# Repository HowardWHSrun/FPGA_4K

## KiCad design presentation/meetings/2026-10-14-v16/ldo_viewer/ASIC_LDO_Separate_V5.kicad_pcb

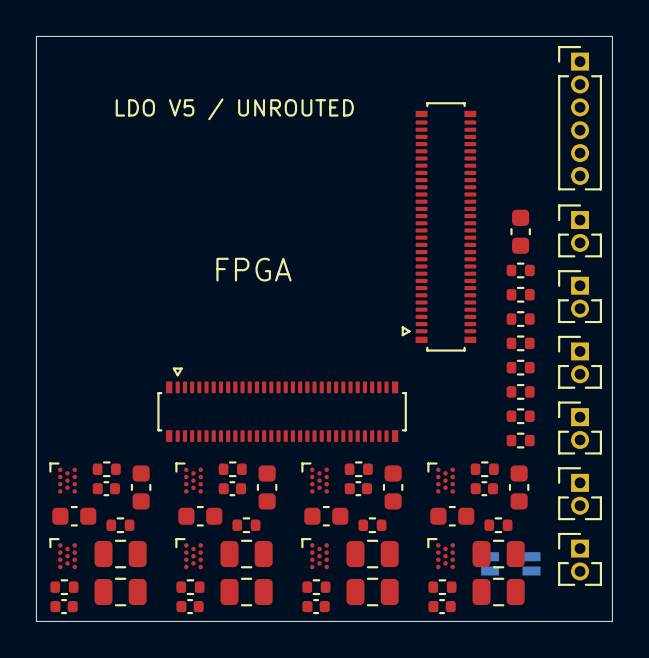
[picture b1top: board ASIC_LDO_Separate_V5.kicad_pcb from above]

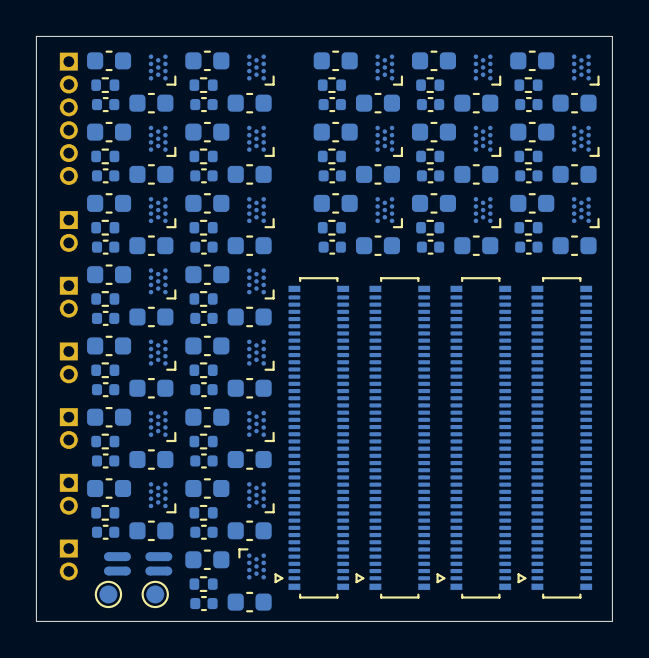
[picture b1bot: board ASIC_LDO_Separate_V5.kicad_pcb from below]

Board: 2 copper layers, 32.0 x 32.5 mm, 192 parts (130 on the bottom side), 203 nets, no tracks yet.

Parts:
C90: 10uF 10V - provisional bulk; C_0603_1608Metric
C101, C103, C104, C106, C107, C109, C110, C112, C113, C115, C116, C118, C119, C121, C201, C203, C204, C206, C207, C209, C210, C212, C213, C215, C216, C218, C219, C221, C301, C303, C304, C306, C307, C309, C310, C312, C313, C315, C316, C318, C319, C321, C401, C403, C404, C406, C407, C409, C410, C412, C413, C415, C416, C418, C419, C421: 10uF 10V; C_0603_1608Metric
C102, C105, C108, C111, C114, C117, C120, C202, C205, C208, C211, C214, C217, C220, C302, C305, C308, C311, C314, C317, C320, C402, C405, C408, C411, C414, C417, C420: 1uF 10V; C_0402_1005Metric
C122, C124, C222, C224, C322, C324, C422, C424: 10uF 25V; C_0805_2012Metric
C123, C223, C323, C423: 1uF 25V; C_0402_1005Metric
J1, J2: DF40C-60DP-0.4V(51); Hirose_DF40C-60DP-0.4V_2x30-1MP_P0.4mm
J10: ASIC 3.3 V external input; Harwin_M50-3530242_1x02_P1.27mm_Vertical
J90: Positive high-rail raw input; Harwin_M50-3530242_1x02_P1.27mm_Vertical
J91: Four regulated VSS10 inputs + returns; Harwin_M50-3530642_1x06_P1.27mm_Vertical
J101, J201, J301, J401: DF40C-80DP-0.4V(51); Hirose_DF40C-80DP-0.4V_2x40-1MP_P0.4mm
J102, J202, J302, J402: AC_IN provision - external analog source; Harwin_M50-3530242_1x02_P1.27mm_Vertical
NT100, NT200, NT300, NT400: AGND / DGND bond; NetTie-2_SMD_Pad0.5mm
R101, R102, R103, R104, R105, R201, R202, R203, R204, R205, R301, R302, R303, R304, R305, R401, R402, R403, R404, R405: 15k 1%; R_0402_1005Metric
R106, R206, R306, R406: 16k 1%; R_0402_1005Metric
R107, R207, R307, R407: 7.5k 1%; R_0402_1005Metric
R108, R208, R308, R408: 90k 1%; R_0402_1005Metric
R109, R209, R309, R409: 68k 1%; R_0402_1005Metric
R250, R251, R252, R253, R450, R451, R452, R453: 10k 1%; R_0402_1005Metric
TP90: ASIC_3V3 probe; TestPoint_Pad_D1.0mm
TP91: GND probe; TestPoint_Pad_D1.0mm
U101, U102, U103, U104, U105, U106, U107, U108, U201, U202, U203, U204, U205, U206, U207, U208, U301, U302, U303, U304, U305, U306, U307, U308, U401, U402, U403, U404, U405, U406, U407, U408: LT3046ANQ+T; LT3046_WLCSP_11_NQ

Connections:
ASIC1_CLK32MHz_Out: J1.9, J101.45
ASIC1_DATA1: J1.1, J101.79
ASIC1_DATA2: J1.2, J101.77
ASIC1_DATA3: J1.3, J101.75
ASIC1_DATA4: J1.4, J101.73
ASIC1_DATA5: J1.5, J101.43
ASIC1_DATA6: J1.6, J101.41
ASIC1_DATA7: J1.7, J101.39
ASIC1_DATA8: J1.8, J101.37
ASIC1_READ: J1.10, J101.35
ASIC1_SYNC: J1.11, J101.47
ASIC2_CLK32MHz_Out: J1.20, J101.19
ASIC2_DATA1: J1.12, J101.33
ASIC2_DATA2: J1.13, J101.31
ASIC2_DATA3: J1.14, J101.29
ASIC2_DATA4: J1.15, J101.27
ASIC2_DATA5: J1.16, J101.17
ASIC2_DATA6: J1.17, J101.15
ASIC2_DATA7: J1.18, J101.13
ASIC2_DATA8: J1.19, J101.11
ASIC2_READ: J1.21, J101.9
ASIC2_SYNC: J1.22, J101.21
ASIC3_CLK32MHz_Out: J1.32, J201.45
ASIC3_DATA1: J1.23, J201.79
ASIC3_DATA2: J1.24, J201.77
ASIC3_DATA3: J1.25, J201.75
ASIC3_DATA4: J1.26, J201.73
ASIC3_DATA5: J1.27, J201.43
ASIC3_DATA6: J1.28, J201.41
ASIC3_DATA7: J1.29, J201.39
ASIC3_DATA8: J1.31, J201.37
ASIC3_READ: J1.33, J201.35
ASIC3_SYNC: J1.34, J201.47
ASIC4_CLK32MHz_Out: J1.43, J201.19
ASIC4_DATA1: J1.35, J201.33
ASIC4_DATA2: J1.36, J201.31
ASIC4_DATA3: J1.37, J201.29
ASIC4_DATA4: J1.38, J201.27
ASIC4_DATA5: J1.39, J201.17
ASIC4_DATA6: J1.40, J201.15
ASIC4_DATA7: J1.41, J201.13
ASIC4_DATA8: J1.42, J201.11
ASIC4_READ: J1.44, J201.9
ASIC4_SYNC: J1.45, J201.21
ASIC5_CLK32MHz_Out: J2.9, J301.45
ASIC5_DATA1: J2.1, J301.79
ASIC5_DATA2: J2.2, J301.77
ASIC5_DATA3: J2.3, J301.75
ASIC5_DATA4: J2.4, J301.73
ASIC5_DATA5: J2.5, J301.43
ASIC5_DATA6: J2.6, J301.41
ASIC5_DATA7: J2.7, J301.39
ASIC5_DATA8: J2.8, J301.37
ASIC5_READ: J2.10, J301.35
ASIC5_SYNC: J2.11, J301.47
ASIC6_CLK32MHz_Out: J2.20, J301.19
ASIC6_DATA1: J2.12, J301.33
ASIC6_DATA2: J2.13, J301.31
ASIC6_DATA3: J2.14, J301.29
ASIC6_DATA4: J2.15, J301.27
ASIC6_DATA5: J2.16, J301.17
ASIC6_DATA6: J2.17, J301.15
ASIC6_DATA7: J2.18, J301.13
ASIC6_DATA8: J2.19, J301.11
ASIC6_READ: J2.21, J301.9
ASIC6_SYNC: J2.22, J301.21
ASIC7_CLK32MHz_Out: J2.32, J401.45
ASIC7_DATA1: J2.23, J401.79
ASIC7_DATA2: J2.24, J401.77
ASIC7_DATA3: J2.25, J401.75
ASIC7_DATA4: J2.26, J401.73
ASIC7_DATA5: J2.27, J401.43
ASIC7_DATA6: J2.28, J401.41
ASIC7_DATA7: J2.29, J401.39
ASIC7_DATA8: J2.31, J401.37
ASIC7_READ: J2.33, J401.35
ASIC7_SYNC: J2.34, J401.47
ASIC8_CLK32MHz_Out: J2.43, J401.19
ASIC8_DATA1: J2.35, J401.33
ASIC8_DATA2: J2.36, J401.31
ASIC8_DATA3: J2.37, J401.29
ASIC8_DATA4: J2.38, J401.27
ASIC8_DATA5: J2.39, J401.17
ASIC8_DATA6: J2.40, J401.15
ASIC8_DATA7: J2.41, J401.13
ASIC8_DATA8: J2.42, J401.11
ASIC8_READ: J2.44, J401.9
ASIC8_SYNC: J2.45, J401.21
ASIC_3V3: C90.1, C101.1, C104.1, C107.1, C110.1, C113.1, C116.1, C119.1, C201.1, C204.1, C207.1, C210.1, C213.1, C216.1, C219.1, C301.1, C304.1, C307.1, C310.1, C313.1, C316.1, C319.1, C401.1, C404.1, C407.1, C410.1, C413.1, C416.1, C419.1, J10.1, TP90.1 (1_1), U101.A3 (IN), U101.B3 (EN/UV), U101.F1 (PGFB), U102.A3 (IN), U102.B3 (EN/UV), U102.F1 (PGFB), U103.A3 (IN), U103.B3 (EN/UV), U103.F1 (PGFB), U104.A3 (IN), U104.B3 (EN/UV), U104.F1 (PGFB), U105.A3 (IN), U105.B3 (EN/UV), U105.F1 (PGFB), U106.A3 (IN), U106.B3 (EN/UV), U106.F1 (PGFB), U107.A3 (IN), U107.B3 (EN/UV), U107.F1 (PGFB), U201.A3 (IN), U201.B3 (EN/UV), U201.F1 (PGFB), U202.A3 (IN), U202.B3 (EN/UV), U202.F1 (PGFB), U203.A3 (IN), U203.B3 (EN/UV), U203.F1 (PGFB), U204.A3 (IN), U204.B3 (EN/UV), U204.F1 (PGFB), U205.A3 (IN), U205.B3 (EN/UV), U205.F1 (PGFB), U206.A3 (IN), U206.B3 (EN/UV), U206.F1 (PGFB), U207.A3 (IN), U207.B3 (EN/UV), U207.F1 (PGFB), U301.A3 (IN), U301.B3 (EN/UV), U301.F1 (PGFB), U302.A3 (IN), U302.B3 (EN/UV), U302.F1 (PGFB), U303.A3 (IN), U303.B3 (EN/UV), U303.F1 (PGFB), U304.A3 (IN), U304.B3 (EN/UV), U304.F1 (PGFB), U305.A3 (IN), U305.B3 (EN/UV), U305.F1 (PGFB), U306.A3 (IN), U306.B3 (EN/UV), U306.F1 (PGFB), U307.A3 (IN), U307.B3 (EN/UV), U307.F1 (PGFB), U401.A3 (IN), U401.B3 (EN/UV), U401.F1 (PGFB), U402.A3 (IN), U402.B3 (EN/UV), U402.F1 (PGFB), U403.A3 (IN), U403.B3 (EN/UV), U403.F1 (PGFB), U404.A3 (IN), U404.B3 (EN/UV), U404.F1 (PGFB), U405.A3 (IN), U405.B3 (EN/UV), U405.F1 (PGFB), U406.A3 (IN), U406.B3 (EN/UV), U406.F1 (PGFB), U407.A3 (IN), U407.B3 (EN/UV), U407.F1 (PGFB)
B1_AC_IN: J101.69, J102.1
B1_AGND: C101.2, C102.2, C103.2, C107.2, C108.2, C109.2, C110.2, C111.2, C112.2, C113.2, C114.2, C115.2, C116.2, C117.2, C118.2, C119.2, C120.2, C121.2, C122.2, C123.2, C124.2, J101.42, J101.44, J102.2, NT100.1, R101.2, R103.2, R104.2, R105.2, R106.2, R107.2, R108.2, R109.2, U101.E1 (GND), U101.F3 (ILIM), U103.E1 (GND), U103.F3 (ILIM), U104.E1 (GND), U104.F3 (ILIM), U105.E1 (GND), U105.F3 (ILIM), U106.E1 (GND), U106.F3 (ILIM), U107.E1 (GND), U107.F3 (ILIM), U108.E1 (GND), U108.F3 (ILIM)
B1_DVDD: C112.1, J101.34, U104.A1 (OUT), U104.Aa2 (OUT), U104.B1 (OUTS)
B1_REF_VCM: C121.1, J101.40, R109.1, U107.A1 (OUT), U107.Aa2 (OUT), U107.B1 (OUTS)
B1_REF_VDD: C115.1, J101.52, U105.A1 (OUT), U105.Aa2 (OUT), U105.B1 (OUTS)
B1_VDD10: C124.1, J101.36, U108.A1 (OUT), U108.Aa2 (OUT), U108.B1 (OUTS)
B1_VDD_ADC: C106.1, J101.56, U102.A1 (OUT), U102.Aa2 (OUT), U102.B1 (OUTS)
B1_VDD_CGEN: C118.1, J101.1, U106.A1 (OUT), U106.Aa2 (OUT), U106.B1 (OUTS)
B1_VDD_DRIVER: C109.1, J101.38, U103.A1 (OUT), U103.Aa2 (OUT), U103.B1 (OUTS)
B1_VDD_FE: C103.1, J101.50, U101.A1 (OUT), U101.Aa2 (OUT), U101.B1 (OUTS)
B1_VSS10: J91.2, J101.54
B2_AC_IN: J201.69, J202.1
B2_AGND: C201.2, C202.2, C203.2, C207.2, C208.2, C209.2, C210.2, C211.2, C212.2, C213.2, C214.2, C215.2, C216.2, C217.2, C218.2, C219.2, C220.2, C221.2, C222.2, C223.2, C224.2, J201.42, J201.44, J202.2, NT200.1, R201.2, R203.2, R204.2, R205.2, R206.2, R207.2, R208.2, R209.2, U201.E1 (GND), U201.F3 (ILIM), U203.E1 (GND), U203.F3 (ILIM), U204.E1 (GND), U204.F3 (ILIM), U205.E1 (GND), U205.F3 (ILIM), U206.E1 (GND), U206.F3 (ILIM), U207.E1 (GND), U207.F3 (ILIM), U208.E1 (GND), U208.F3 (ILIM)
B2_DVDD: C212.1, J201.34, U204.A1 (OUT), U204.Aa2 (OUT), U204.B1 (OUTS)
B2_REF_VCM: C221.1, J201.40, R209.1, U207.A1 (OUT), U207.Aa2 (OUT), U207.B1 (OUTS)
B2_REF_VDD: C215.1, J201.52, U205.A1 (OUT), U205.Aa2 (OUT), U205.B1 (OUTS)
B2_STIM_CHB_IDLE: J201.49, R250.1
B2_STIM_CLK_IDLE: J201.53, R252.1
B2_STIM_EN_IDLE: J201.51, R251.1
B2_STIM_START_IDLE: J201.55, R253.1
B2_VDD10: C224.1, J201.36, U208.A1 (OUT), U208.Aa2 (OUT), U208.B1 (OUTS)
B2_VDD_ADC: C206.1, J201.56, U202.A1 (OUT), U202.Aa2 (OUT), U202.B1 (OUTS)
B2_VDD_CGEN: C218.1, J201.1, U206.A1 (OUT), U206.Aa2 (OUT), U206.B1 (OUTS)
B2_VDD_DRIVER: C209.1, J201.38, U203.A1 (OUT), U203.Aa2 (OUT), U203.B1 (OUTS)
B2_VDD_FE: C203.1, J201.50, U201.A1 (OUT), U201.Aa2 (OUT), U201.B1 (OUTS)
B2_VSS10: J91.3, J201.54
B3_AC_IN: J301.69, J302.1
B3_AGND: C301.2, C302.2, C303.2, C307.2, C308.2, C309.2, C310.2, C311.2, C312.2, C313.2, C314.2, C315.2, C316.2, C317.2, C318.2, C319.2, C320.2, C321.2, C322.2, C323.2, C324.2, J301.42, J301.44, J302.2, NT300.1, R301.2, R303.2, R304.2, R305.2, R306.2, R307.2, R308.2, R309.2, U301.E1 (GND), U301.F3 (ILIM), U303.E1 (GND), U303.F3 (ILIM), U304.E1 (GND), U304.F3 (ILIM), U305.E1 (GND), U305.F3 (ILIM), U306.E1 (GND), U306.F3 (ILIM), U307.E1 (GND), U307.F3 (ILIM), U308.E1 (GND), U308.F3 (ILIM)
B3_DVDD: C312.1, J301.34, U304.A1 (OUT), U304.Aa2 (OUT), U304.B1 (OUTS)
B3_REF_VCM: C321.1, J301.40, R309.1, U307.A1 (OUT), U307.Aa2 (OUT), U307.B1 (OUTS)
B3_REF_VDD: C315.1, J301.52, U305.A1 (OUT), U305.Aa2 (OUT), U305.B1 (OUTS)
B3_VDD10: C324.1, J301.36, U308.A1 (OUT), U308.Aa2 (OUT), U308.B1 (OUTS)
B3_VDD_ADC: C306.1, J301.56, U302.A1 (OUT), U302.Aa2 (OUT), U302.B1 (OUTS)
B3_VDD_CGEN: C318.1, J301.1, U306.A1 (OUT), U306.Aa2 (OUT), U306.B1 (OUTS)
B3_VDD_DRIVER: C309.1, J301.38, U303.A1 (OUT), U303.Aa2 (OUT), U303.B1 (OUTS)
B3_VDD_FE: C303.1, J301.50, U301.A1 (OUT), U301.Aa2 (OUT), U301.B1 (OUTS)
B3_VSS10: J91.4, J301.54
B4_AC_IN: J401.69, J402.1
B4_AGND: C401.2, C402.2, C403.2, C407.2, C408.2, C409.2, C410.2, C411.2, C412.2, C413.2, C414.2, C415.2, C416.2, C417.2, C418.2, C419.2, C420.2, C421.2, C422.2, C423.2, C424.2, J401.42, J401.44, J402.2, NT400.1, R401.2, R403.2, R404.2, R405.2, R406.2, R407.2, R408.2, R409.2, U401.E1 (GND), U401.F3 (ILIM), U403.E1 (GND), U403.F3 (ILIM), U404.E1 (GND), U404.F3 (ILIM), U405.E1 (GND), U405.F3 (ILIM), U406.E1 (GND), U406.F3 (ILIM), U407.E1 (GND), U407.F3 (ILIM), U408.E1 (GND), U408.F3 (ILIM)
B4_DVDD: C412.1, J401.34, U404.A1 (OUT), U404.Aa2 (OUT), U404.B1 (OUTS)
B4_REF_VCM: C421.1, J401.40, R409.1, U407.A1 (OUT), U407.Aa2 (OUT), U407.B1 (OUTS)
B4_REF_VDD: C415.1, J401.52, U405.A1 (OUT), U405.Aa2 (OUT), U405.B1 (OUTS)
B4_STIM_CHB_IDLE: J401.49, R450.1
B4_STIM_CLK_IDLE: J401.53, R452.1
B4_STIM_EN_IDLE: J401.51, R451.1
B4_STIM_START_IDLE: J401.55, R453.1
B4_VDD10: C424.1, J401.36, U408.A1 (OUT), U408.Aa2 (OUT), U408.B1 (OUTS)
B4_VDD_ADC: C406.1, J401.56, U402.A1 (OUT), U402.Aa2 (OUT), U402.B1 (OUTS)
B4_VDD_CGEN: C418.1, J401.1, U406.A1 (OUT), U406.Aa2 (OUT), U406.B1 (OUTS)
B4_VDD_DRIVER: C409.1, J401.38, U403.A1 (OUT), U403.Aa2 (OUT), U403.B1 (OUTS)
B4_VDD_FE: C403.1, J401.50, U401.A1 (OUT), U401.Aa2 (OUT), U401.B1 (OUTS)
B4_VSS10: J91.5, J401.54
BOARD1_CLK: J1.46, J101.7
BOARD1_SPI_CLK: J1.48, J101.63
BOARD2_CLK: J1.47, J201.7
BOARD2_SPI_CLK: J1.49, J201.63
BOARD3_CLK: J2.46, J301.7
BOARD3_SPI_CLK: J2.48, J301.63
BOARD4_CLK: J2.47, J401.7
BOARD4_SPI_CLK: J2.49, J401.63
CHIP_RESET_SHARED: J1.56, J101.71, J201.71, J301.71, J401.71
FE_RESET_SHARED: J1.57, J101.65, J201.65, J301.65, J401.65
GND: C90.2, C104.2, C105.2, C106.2, C204.2, C205.2, C206.2, C304.2, C305.2, C306.2, C404.2, C405.2, C406.2, J1.30, J2.30, J10.2, J90.2, J91.1, J91.6, J101.46, J101.48, J201.46, J201.48, J301.46, J301.48, J401.46, J401.48, NT100.2, NT200.2, NT300.2, NT400.2, R102.2, R202.2, R250.2, R251.2, R252.2, R253.2, R302.2, R402.2, R450.2, R451.2, R452.2, R453.2, TP91.1 (1_1), U102.E1 (GND), U102.F3 (ILIM), U202.E1 (GND), U202.F3 (ILIM), U302.E1 (GND), U302.F3 (ILIM), U402.E1 (GND), U402.F3 (ILIM)
IMP_TST_SHARED: J1.58, J101.67, J201.67, J301.67, J401.67
NONSTIM_BOARD1_SPI_DL: J1.54, J201.25, J201.59
NONSTIM_BOARD1_SPI_DR: J1.55, J201.23, J201.57
NONSTIM_BOARD2_SPI_DL: J2.54, J401.25, J401.59
NONSTIM_BOARD2_SPI_DR: J2.55, J401.23, J401.57
unnamed: C102.1, R101.1, U101.Ea2 (SET)
unnamed: C105.1, R102.1, U102.Ea2 (SET)
unnamed: C108.1, R103.1, U103.Ea2 (SET)
unnamed: C111.1, R104.1, U104.Ea2 (SET)
unnamed: C114.1, R105.1, U105.Ea2 (SET)
unnamed: C117.1, R106.1, U106.Ea2 (SET)
unnamed: C120.1, R107.1, U107.Ea2 (SET)
unnamed: C123.1, R108.1, U108.Ea2 (SET)
unnamed: C202.1, R201.1, U201.Ea2 (SET)
unnamed: C205.1, R202.1, U202.Ea2 (SET)
unnamed: C208.1, R203.1, U203.Ea2 (SET)
unnamed: C211.1, R204.1, U204.Ea2 (SET)
unnamed: C214.1, R205.1, U205.Ea2 (SET)
unnamed: C217.1, R206.1, U206.Ea2 (SET)
unnamed: C220.1, R207.1, U207.Ea2 (SET)
unnamed: C223.1, R208.1, U208.Ea2 (SET)
unnamed: C302.1, R301.1, U301.Ea2 (SET)
unnamed: C305.1, R302.1, U302.Ea2 (SET)
unnamed: C308.1, R303.1, U303.Ea2 (SET)
unnamed: C311.1, R304.1, U304.Ea2 (SET)
unnamed: C314.1, R305.1, U305.Ea2 (SET)
unnamed: C317.1, R306.1, U306.Ea2 (SET)
unnamed: C320.1, R307.1, U307.Ea2 (SET)
unnamed: C323.1, R308.1, U308.Ea2 (SET)
unnamed: C402.1, R401.1, U401.Ea2 (SET)
unnamed: C405.1, R402.1, U402.Ea2 (SET)
unnamed: C408.1, R403.1, U403.Ea2 (SET)
unnamed: C411.1, R404.1, U404.Ea2 (SET)
unnamed: C414.1, R405.1, U405.Ea2 (SET)
unnamed: C417.1, R406.1, U406.Ea2 (SET)
unnamed: C420.1, R407.1, U407.Ea2 (SET)
unnamed: C423.1, R408.1, U408.Ea2 (SET)
SPI_LATCH_SHARED: J1.59, J101.61, J201.61, J301.61, J401.61
STIM_CHB_SHARED: J2.59, J101.49, J301.49
STIM_CHIP1_SPI_DL: J1.50, J101.59
STIM_CHIP1_SPI_DR: J1.51, J101.57
STIM_CHIP2_SPI_DL: J1.52, J101.25
STIM_CHIP2_SPI_DR: J1.53, J101.23
STIM_CHIP3_SPI_DL: J2.50, J301.59
STIM_CHIP3_SPI_DR: J2.51, J301.57
STIM_CHIP4_SPI_DL: J2.52, J301.25
STIM_CHIP4_SPI_DR: J2.53, J301.23
STIM_CLK_SHARED: J2.56, J101.53, J301.53
STIM_EN_SHARED: J2.58, J101.51, J301.51
STIM_POS_RAW: C122.1, C222.1, C322.1, C422.1, J90.1, U108.A3 (IN), U108.B3 (EN/UV), U108.F1 (PGFB), U208.A3 (IN), U208.B3 (EN/UV), U208.F1 (PGFB), U308.A3 (IN), U308.B3 (EN/UV), U308.F1 (PGFB), U408.A3 (IN), U408.B3 (EN/UV), U408.F1 (PGFB)
STIM_START_SHARED: J2.57, J101.55, J301.55

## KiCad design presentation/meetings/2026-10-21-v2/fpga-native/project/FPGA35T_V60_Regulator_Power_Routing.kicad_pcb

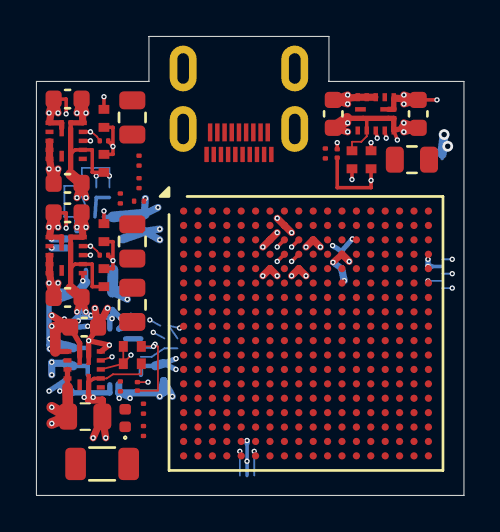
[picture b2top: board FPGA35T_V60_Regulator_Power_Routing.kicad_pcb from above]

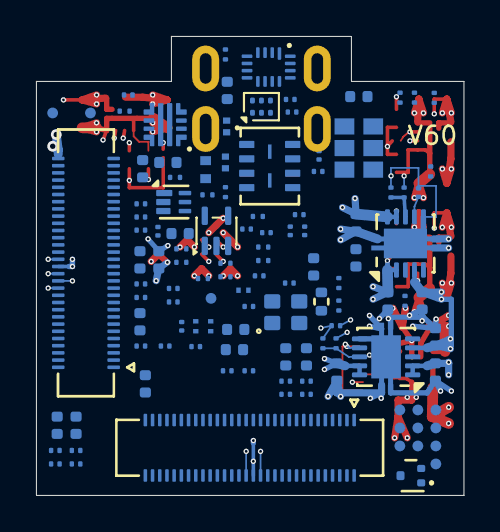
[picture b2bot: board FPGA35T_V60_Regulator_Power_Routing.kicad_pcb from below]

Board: 10 copper layers, 23.8 x 25.5 mm, 157 parts (117 on the bottom side), 186 nets.

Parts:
C1, C2, C12, C13, C21, C22, C86: 22uF; C_0603_1608Metric
C3, C14, C23, C87: 22pF; C_0201_GRM03_Murata_0p22Gap
C4: 100uF; C_1206_3216Metric
C5, C6, C16, C17, C24, C25, C30, C31, C36, C37, C43, C44, C45, C47, C48, C49, C51, C54: 4.7uF; C_0402_1005Metric
C7, C8, C9, C11, C18, C19, C20, C26, C27, C28, C29, C32, C33, C34, C35, C38, C39, C40, C41, C57, C58: 470nF; C_0201_GRM03_Murata_0p22Gap
C10, C15, C42, C59: 47uF; C_0805_2012Metric
C46, C50: 10nF; C_0201_GRM03_Murata_0p22Gap
C52, C53, C55, C56, C60, C63, C78, C79, C80, C82, C83, C88: 100nF; C_0201_GRM03_Murata_0p22Gap
C61, C84: 1uF; C_0402_1005Metric
C62: 220nF; C_0201_GRM03_Murata_0p22Gap
C75: 1uF / 25V; C_0402_1005Metric
C76: 1uF / 10V; C_0402_1005Metric
C77: 3.3nF / 25V; C_0201_GRM03_Murata_0p22Gap
C81: 10uF; C_0402_1005Metric
C85: 22uF; C_0805_2012Metric
D1: SML-P11UTT86R / RED; ROHM_SML_P11_1006
J1, J2: DF40C-60DS-0.4V(51); Hirose_DF40C-60DS-0.4V_2x30_P0.4mm
J3: Micro-HDMI 467651001; Molex_MicroHDMI_46765_1xxx
L1, L2, L3: MPZ0603S121HT000; TDK_MPZ0603S121HT000_0201_Land_0p25x0p30_Gap0p30
Q1: RYM002N05T2CL; ROHM_VMT3_SOT723
R1, R4, R41: 200k; R_0402_TE_CPF_Reflow_0p50Gap
R2: 301k; R_0402_TE_CPF_Reflow_0p50Gap
R3, R6, R11, R14, R38, R43: 4.99k; R_0201_ERA1A_Panasonic_0p30Gap
R5, R8: 100k; R_0402_TE_CPF_Reflow_0p50Gap
R7, R42: 150k; R_0402_TE_CPF_Reflow_0p50Gap
R9, R12, R40, R46, R47, R48: 10k; R_0201_ERA1A_Panasonic_0p30Gap
R10: 1.24k; R_0201_ERA1A_Panasonic_0p30Gap
R13: 2.49k; R_0201_ERA1A_Panasonic_0p30Gap
R16: 100R; R_0201_ERA1A_Panasonic_0p30Gap
R17, R18, R19, R20, R21, R22, R49, R50: 4.7k; R_0201_ERA1A_Panasonic_0p30Gap
R25: 470R; R_0201_ERA1A_Panasonic_0p30Gap
R27: 1k; R_0201_ERA1A_Panasonic_0p30Gap
R34: 174k; R_0402_TE_CPF_Reflow_0p50Gap
R35: 24.9k; R_0201_Yageo_RT_RE_Reflow_1p00Span
R36: 100k; R_0201_Yageo_RT_RE_Reflow_1p00Span
R37: 6.49k; R_0201_ERA1A_Panasonic_0p30Gap
R39: 1.5k; R_0201_ERA1A_Panasonic_0p30Gap
R44: 33R; R_0402_1005Metric
R45: 4.64k; R_0201_ERA1A_Panasonic_0p30Gap
R51, R52, R53: 47k; R_0201_ERA1A_Panasonic_0p30Gap
R54: 22k; R_0201_ERA1A_Panasonic_0p30Gap
TP1, TP2, TP3, TP4, TP5, TP6, TP7, TP8, TP9, TP10, TP11, TP12, TP13: 0.6mm COPPER; TestPoint_Pad_D0.6mm_Edge_NoPaste
U1: XC7A35T-2CSG325I; Xilinx_CSG325
U2, U3, U4, U13: MPM3834CGPA; MPM3834C_ECLGA14_2.5x2.5mm
U5, U6: TPS74801DRCRM3; VSON-10-1EP_3x3mm_P0.5mm_EP1.65x2.4mm
U7: IS25WP032D-JTLE; ISSI_USON8_4x3mm_T
U8: SN74AVC4T774RSVR / SPI x1; TI_RSV_UQFN16_1.8x2.6mm_P0.4mm
U10: TPS259470ARPWR; TI_RPW0010A_HotRod_2x2mm
U11: 74AUP2G07GM / dual reset OD; Nexperia_SOT886_XSON6_1x1.45mm
U12: TPS389001 / timed rail-ready reset; TI_DSE0006A_WSON6_1p5x1p5_P0p5_Manufacturer
U14: SN74AUP1G14 / SPI OE; TI_DCK_SC70_5
Y1: AX3DCF1-125.0000T3 / 125 MHz; Abracon_AX3_3225_6pin
Y2: SiT1615A / 25 MHz / 1.5 V; SiTime_2016_4pin

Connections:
1V4_GTP_IN: C43.2, C47.2, C86.1, C87.1, R41.1, U5.1 (IN), U5.2 (IN), U6.1 (IN), U6.2 (IN), U13.6 (OUT_S), U13.9 (OUT), U13.10 (OUT)
/ASIC1_CLK32MHz_Out: J1.9, U1.P14 (L12P_T1_MRCC)
/ASIC1_DATA1: J1.1, U1.J14 (L5P_T0_D06)
/ASIC1_DATA2: J1.2, U1.V16 (L18P_T2_A12_D28)
/ASIC1_DATA3: J1.3, U1.V17 (L18N_T2_A11_D27)
/ASIC1_DATA4: J1.4, U1.K15 (L5N_T0_D07)
/ASIC1_DATA5: J1.5, U1.K17 (L4P_T0_D04)
/ASIC1_DATA6: J1.6, U1.K18 (L3N_T0_DQS_EMCCLK)
/ASIC1_DATA7: J1.7, U1.L14 (IO0)
/ASIC1_DATA8: J1.8, U1.L18 (L4N_T0_D05)
/ASIC1_READ: J1.10, U1.M14 (L8P_T1_D11)
/ASIC1_SYNC: J1.11, U1.M16 (L7P_T1_D09)
/ASIC2_CLK32MHz_Out: J1.20, U1.T14 (L13P_T2_MRCC)
/ASIC2_DATA1: J1.12, U1.M17 (L7N_T1_D10)
/ASIC2_DATA2: J1.13, U1.N14 (L8N_T1_D12)
/ASIC2_DATA3: J1.14, U1.N16 (L9P_T1_DQS)
/ASIC2_DATA4: J1.15, U1.N17 (L9N_T1_DQS_D13)
/ASIC2_DATA5: J1.16, U1.N18 (L10P_T1_D14)
/ASIC2_DATA6: J1.17, U1.P16 (L11N_T1_SRCC)
/ASIC2_DATA7: J1.18, U1.P18 (L10N_T1_D15)
/ASIC2_DATA8: J1.19, U1.R13 (L19P_T3_A10_D26)
/ASIC2_READ: J1.21, U1.R15 (L12N_T1_MRCC)
/ASIC2_SYNC: J1.22, U1.R17 (L14N_T2_SRCC)
/ASIC3_CLK32MHz_Out: J1.32, U1.P15 (L11P_T1_SRCC)
/ASIC3_DATA1: J1.23, U1.R18 (L15P_T2_DQS_RDWR_B)
/ASIC3_DATA2: J1.24, U1.T12 (L22P_T3_A05_D21)
/ASIC3_DATA3: J1.25, U1.T15 (L13N_T2_MRCC)
/ASIC3_DATA4: J1.26, U1.T17 (L16P_T2_CSI_B)
/ASIC3_DATA5: J1.27, U1.T18 (L15N_T2_DQS_DOUT_CSO_B)
/ASIC3_DATA6: J1.28, U1.U9 (L24P_T3_A01_D17)
/ASIC3_DATA7: J1.29, U1.U10 (IO25)
/ASIC3_DATA8: J1.31, U1.U11 (L23P_T3_A03_D19)
/ASIC3_READ: J1.33, U1.U12 (L22N_T3_A04_D20)
/ASIC3_SYNC: J1.34, U1.U14 (L20P_T3_A08_D24)
/ASIC4_CLK32MHz_Out: J1.43, U1.E13 (L12P_T1_MRCC)
/ASIC4_DATA1: J1.35, U1.A9 (L3N_T0_DQS_AD1N)
/ASIC4_DATA2: J1.36, U1.A10 (L5N_T0_AD9N)
/ASIC4_DATA3: J1.37, U1.A12 (L7N_T1_AD2N)
/ASIC4_DATA4: J1.38, U1.A13 (L8P_T1_AD10P)
/ASIC4_DATA5: J1.39, U1.A14 (L8N_T1_AD10N)
/ASIC4_DATA6: J1.40, U1.A15 (L10N_T1_AD11N)
/ASIC4_DATA7: J1.41, U1.A17 (L15N_T2_DQS_ADV_B)
/ASIC4_DATA8: J1.42, U1.B9 (L3P_T0_DQS_AD1P)
/ASIC4_READ: J1.44, U1.B10 (L5P_T0_AD9P)
/ASIC4_SYNC: J1.45, U1.B11 (L4N_T0)
/ASIC5_CLK32MHz_Out: J2.9, U1.E15 (L13P_T2_MRCC)
/ASIC5_DATA1: J2.1, U1.B12 (L7P_T1_AD2P)
/ASIC5_DATA2: J2.2, U1.B14 (L10P_T1_AD11P)
/ASIC5_DATA3: J2.3, U1.B15 (L9N_T1_DQS_AD3N)
/ASIC5_DATA4: J2.4, U1.B16 (L15P_T2_DQS)
/ASIC5_DATA5: J2.5, U1.B17 (L16N_T2_A27)
/ASIC5_DATA6: J2.6, U1.C8 (L1N_T0_AD0N)
/ASIC5_DATA7: J2.7, U1.C9 (L2N_T0_AD8N)
/ASIC5_DATA8: J2.8, U1.C11 (L4P_T0)
/ASIC5_READ: J2.10, U1.C13 (L11N_T1_SRCC)
/ASIC5_SYNC: J2.11, U1.C14 (L9P_T1_DQS_AD3P)
/ASIC6_CLK32MHz_Out: J2.20, U1.D13 (L11P_T1_SRCC)
/ASIC6_DATA1: J2.12, U1.C16 (L16P_T2_A28)
/ASIC6_DATA2: J2.13, U1.C17 (L18P_T2_A24)
/ASIC6_DATA3: J2.14, U1.C18 (L18N_T2_A23)
/ASIC6_DATA4: J2.15, U1.D8 (L1P_T0_AD0P)
/ASIC6_DATA5: J2.16, U1.D9 (L2P_T0_AD8P)
/ASIC6_DATA6: J2.17, U1.D10 (IO0)
/ASIC6_DATA7: J2.18, U1.D11 (L6P_T0)
/ASIC6_DATA8: J2.19, U1.D14 (L12N_T1_MRCC)
/ASIC6_READ: J2.21, U1.D15 (L13N_T2_MRCC)
/ASIC6_SYNC: J2.22, U1.D16 (L14N_T2_SRCC)
/ASIC7_CLK32MHz_Out: J2.32, U1.P4 (L12P_T1_MRCC)
/ASIC7_DATA1: J2.23, U1.J4 (L2N_T0)
/ASIC7_DATA2: J2.24, U1.J5 (L2P_T0)
/ASIC7_DATA3: J2.25, U1.J6 (IO0)
/ASIC7_DATA4: J2.26, U1.K1 (L3N_T0_DQS)
/ASIC7_DATA5: J2.27, U1.K2 (L3P_T0_DQS)
/ASIC7_DATA6: J2.28, U1.K3 (L4P_T0)
/ASIC7_DATA7: J2.29, U1.K5 (L1N_T0)
/ASIC7_DATA8: J2.31, U1.K6 (L1P_T0)
/ASIC7_READ: J2.33, U1.L2 (L4N_T0)
/ASIC7_SYNC: J2.34, U1.L3 (L5N_T0)
/ASIC8_CLK32MHz_Out: J2.43, U1.R2 (L13P_T2_MRCC)
/ASIC8_DATA1: J2.35, U1.L4 (L5P_T0)
/ASIC8_DATA2: J2.36, U1.L5 (L6P_T0)
/ASIC8_DATA3: J2.37, U1.M1 (L7N_T1)
/ASIC8_DATA4: J2.38, U1.M2 (L7P_T1)
/ASIC8_DATA5: J2.39, U1.M4 (L10P_T1)
/ASIC8_DATA6: J2.40, U1.M6 (L8P_T1)
/ASIC8_DATA7: J2.41, U1.N1 (L9P_T1_DQS)
/ASIC8_DATA8: J2.42, U1.N2 (L11N_T1_SRCC)
/ASIC8_READ: J2.44, U1.N4 (L10N_T1)
/ASIC8_SYNC: J2.45, U1.N6 (L8N_T1)
/CHIP_RESET_SHARED: J1.56, U1.T3 (L17N_T2)
/CLK25_RAW: R44.1, Y2.3 (OUT)
/CLK25_VDD: C88.1, L3.2, Y2.4 (VDD)
/FB_GTP_1V4: C87.2, R41.2, R42.1, U13.5 (FB)
/FE_RESET_SHARED: J1.57, U1.T4 (L17P_T2)
/IMP_TST_SHARED: J1.58, U1.D18 (L17N_T2_A25)
/LED_USER_A: D1.2 (A), R39.2
/LED_USER_K: D1.1 (K), Q1.3 (D)
/NONSTIM_BOARD1_SPI_DL: J1.54, U1.T5 (L21N_T3_DQS)
/NONSTIM_BOARD1_SPI_DR: J1.55, U1.E17 (L17P_T2_A26)
/NONSTIM_BOARD2_SPI_DL: J2.54, U1.T7 (L22N_T3)
/NONSTIM_BOARD2_SPI_DR: J2.55, U1.E18 (L24N_T3_RS0)
/OSC125_N: C79.1, Y1.5 (OUTN)
/OSC125_P: C78.1, Y1.4 (OUTP)
/STIM_CHIP1_SPI_DL: J1.50, U1.U2 (L15P_T2_DQS)
/STIM_CHIP1_SPI_DR: J1.51, U1.U15 (L17P_T2_A14_D30)
/STIM_CHIP2_SPI_DL: J1.52, U1.F15 (L21N_T3_DQS_A18)
/STIM_CHIP2_SPI_DR: J1.53, U1.U4 (L18P_T2)
/STIM_CHIP3_SPI_DL: J2.50, U1.U16 (L17N_T2_A13_D29)
/STIM_CHIP3_SPI_DR: J2.51, U1.F17 (L24P_T3_RS1)
/STIM_CHIP4_SPI_DL: J2.52, U1.U5 (L20N_T3)
/STIM_CHIP4_SPI_DR: J2.53, U1.U17 (L16N_T2_A15_D31)
BOARD1_CLK: J1.46, U1.P1 (L9N_T1_DQS)
BOARD1_SPI_CLK: J1.48, U1.P3 (L12N_T1_MRCC)
BOARD2_CLK: J1.47, U1.P6 (L19P_T3)
BOARD2_SPI_CLK: J1.49, U1.R1 (L13N_T2_MRCC)
BOARD3_CLK: J2.46, U1.R5 (L21P_T3_DQS)
BOARD3_SPI_CLK: J2.48, U1.R6 (IO25)
BOARD4_CLK: J2.47, U1.R7 (L22P_T3)
BOARD4_SPI_CLK: J2.49, U1.T2 (L14N_T2_SRCC)
BOOT_RAILS_PG_3V3: R9.2, TP10.1 (PAD_1), U4.11 (PG), U6.3 (PG), U12.3 (MR_PG)
BOOT_RESET_N: R47.2, U11.1 (1A_RESET_N), U11.3 (2A_RESET_N), U12.6 (RESET_N_OD), U14.2 (A_RESET_N)
CABLE_TARGET_SENSE: J3.1 (SENSE), R27.2
CLK25_PL: R44.2, U1.N3 (L11P_T1_SRCC)
FLASH_CS_N_1V8: R22.2, U7.1 (CE#), U8.11 (B2_CS)
FLASH_DQ0_1V8: R53.2, U7.5 (SI_/_DQ0), U8.10 (B3_MOSI)
FLASH_DQ1_1V8: R51.1, U7.2 (SO_/_DQ1), U8.9 (B4_MISO)
FLASH_HOLD_N_1V8: R21.2, U7.7 (HOLD#_/_DQ3)
FLASH_READY_SENSE: R45.2, R46.1, U12.1 (SENSE_DIV)
FLASH_SCK_1V8: R52.1, U7.6 (SCK), U8.12 (B1_SCK)
FLASH_TRANSLATOR_OE_N: R48.2, U8.7 (OE_N), U14.4 (Y_OE_N)
FLASH_WP_N_1V8: R20.2, U7.3 (WP#_/_DQ2)
FPGA_DONE: R38.2, TP12.1 (PAD_1), U1.F12 (DONE_0)
FPGA_INIT_B: R18.2, TP11.1 (PAD_1), U1.T10 (INIT_B_0), U11.4 (2Y_INIT_OD)
FPGA_JTAG_TCK: J3.17 (TCK), U1.F8 (TCK_0)
FPGA_JTAG_TDI: J3.15 (TDI), U1.T9 (TDI_0)
FPGA_JTAG_TDO: J3.18 (TDO), U1.T8 (TDO_0)
FPGA_JTAG_TMS: J3.2 (TMS), U1.R8 (TMS_0)
FPGA_LED_USER: Q1.1 (G), R40.1, U1.U7 (L23P_T3)
FPGA_PROGRAM_B: R17.2, U1.P10 (PROGRAM_B_0), U11.6 (1Y_PROGRAM_OD)
FPGA_PUDC_B: R25.2, U1.J18 (L3P_T0_DQS_PUDC_B)
FPGA_QSPI_CCLK: R49.2, U1.E8 (CCLK_0), U8.1 (A1_CCLK)
FPGA_QSPI_CS_N: R19.2, U1.L15 (L6P_T0_FCS_B), U8.2 (A2_CS)
FPGA_QSPI_DQ0: R50.2, U1.K16 (L1P_T0_D00_MOSI), U8.3 (A3_MOSI)
FPGA_QSPI_DQ1: R54.1, U1.L17 (L1N_T0_D01_DIN), U8.4 (A4_MISO)
GND: C1.2, C2.2, C4.2, C5.2, C6.2, C7.2, C8.2, C9.2, C10.2, C11.2, C12.2, C13.2, C15.2, C16.2, C17.2, C18.2, C19.2, C20.2, C21.2, C22.2, C24.2, C25.2, C26.2, C27.2, C28.2, C29.2, C30.2, C31.2, C32.2, C33.2, C34.2, C35.2, C36.2, C37.2, C38.2, C39.2, C40.2, C41.2, C42.2, C43.1, C44.2, C45.2, C46.2, C47.1, C48.2, C49.2, C50.2, C51.2, C52.2, C53.2, C54.2, C55.2, C56.2, C58.2, C59.2, C60.2, C61.2, C62.2, C63.2, C75.2, C76.2, C77.2, C80.2, C81.2, C82.2, C83.2, C84.2, C85.2, C86.2, C88.2, J1.30, J2.30, J3.4 (GND), J3.7 (GND), J3.10 (GND), J3.13 (GND), J3.16 (GND), J3.SH (SHIELD), L2.1, Q1.2 (S), R2.2, R5.2, R8.2, R11.2, R14.2, R36.2, R37.2, R40.2, R42.2, R46.2, R51.2, R52.2, R54.2, TP1.1 (PAD_1), TP13.1 (PAD_1), U1.A1 (GND_[75_balls]), U1.A5 (GND), U1.A7 (GND), U1.A8 (GND), U1.A11 (GND), U1.A18 (GND), U1.B3 (GND), U1.B7 (GND), U1.B8 (GND), U1.B18 (GND), U1.C2 (GND), U1.C3 (MGTPRXN2_216), U1.C4 (MGTPRXP2_216), U1.C6 (GND), U1.C7 (GND), U1.C15 (GND), U1.D3 (GND), U1.D4 (GND), U1.D7 (GND), U1.D12 (GND), U1.E2 (GND), U1.E3 (MGTPRXN0_216), U1.E4 (MGTPRXP0_216), U1.E6 (GND), U1.E7 (GND), U1.E9 (GND), U1.E11 (VCCBATT_0), U1.E12 (CFGBVS_0), U1.F4 (GND), U1.F6 (GND), U1.F10 (GND), U1.F13 (M2_0), U1.F16 (GND), U1.G1 (GND), U1.G3 (MGTPRXN3_216), U1.G4 (MGTPRXP3_216), U1.G5 (GND), U1.G6 (GND), U1.G7 (GND), U1.G9 (GND), U1.G11 (GND), U1.G13 (GND), U1.H3 (GND), U1.H4 (GND), U1.H5 (GND), U1.H6 (GND), U1.H8 (GND), U1.H10 (GND), U1.H12 (GND), U1.J1 (GND), U1.J2 (GND), U1.J3 (GND), U1.J7 (GND), U1.J11 (GND), U1.J13 (GND), U1.J17 (GND), U1.K4 (GND), U1.K8 (GND), U1.K12 (GND), U1.K14 (GND), U1.L1 (GND), U1.L7 (GND), U1.L11 (GND), U1.L13 (GND), U1.M8 (GND), U1.M9 (DXN_0), U1.M10 (DXP_0), U1.M12 (GND), U1.M18 (GND), U1.N5 (GND), U1.N7 (GND), U1.N9 (GND), U1.N11 (GND), U1.N13 (GND), U1.N15 (GND), U1.P2 (GND), U1.P8 (GND), U1.P12 (GND), U1.R9 (GND), U1.R11 (M1_0), U1.T6 (GND), U1.T16 (GND), U1.U3 (GND), U1.U13 (GND), U1.V1 (GND), U1.V10 (GND), U1.V18 (GND), U2.2 (PGND), U2.4 (AGND), U2.7 (PGND), U2.8 (PGND), U3.2 (PGND), U3.4 (AGND), U3.7 (PGND), U3.8 (PGND), U4.2 (PGND), U4.4 (AGND), U4.7 (PGND), U4.8 (PGND), U5.6 (GND), U5.11 (GND_EP), U6.6 (GND), U6.11 (GND_EP), U7.4 (GND_/_optional_tabs), U8.6 (DIR4_L), U8.8 (GND), U10.8 (GND), U11.2 (GND), U12.2 (GND), U13.2 (PGND), U13.4 (AGND), U13.7 (PGND), U13.8 (PGND), U14.3 (GND), Y1.3 (GND), Y2.2 (GND)
GNDADC_XADC: C57.2, L2.2, U1.J9 (GNDADC_0), U1.K9 (VREFN_0), U1.K10 (VP_0), U1.L9 (VN_0), U1.L10 (VREFP_0)
GTP_REFCLK0_N: C79.2, U1.D5 (MGTREFCLK0N_216)
GTP_REFCLK0_P: C78.2, U1.D6 (MGTREFCLK0P_216)
GTP_RX1_N: J3.14 (RX1_N), U1.A3 (MGTPRXN1_216)
GTP_RX1_P: J3.12 (RX1_P), U1.A4 (MGTPRXP1_216)
GTP_TX0_N: J3.5 (TX0_N), U1.H1 (MGTPTXN0_216)
GTP_TX0_P: J3.3 (TX0_P), U1.H2 (MGTPTXP0_216)
GTP_TX1_N: J3.8 (TX1_N), U1.F1 (MGTPTXN1_216)
GTP_TX1_P: J3.6 (TX1_P), U1.F2 (MGTPTXP1_216)
GTP_TX2_N: J3.11 (TX2_N), U1.D1 (MGTPTXN2_216)
GTP_TX2_P: J3.9 (TX2_P), U1.D2 (MGTPTXP2_216)
HDMI_PWR_RAW: C75.1, J3.19 (3V3_IN), R34.1, TP2.1 (PAD_1), U10.5 (IN)
MGTAVCC_1V0: C45.1, C51.1, C52.1, C53.1, R10.1, TP7.1 (PAD_1), U1.B4 (MGTAVCC), U1.C5 (MGTAVCC), U1.E5 (MGTAVCC), U1.F5 (MGTAVCC), U5.9 (OUT), U5.10 (OUT)
MGTAVTT_1V2: C49.1, C54.1, C55.1, C56.1, R13.1, R16.1, TP8.1 (PAD_1), U1.A2 (MGTAVTT), U1.C1 (MGTAVTT), U1.E1 (MGTAVTT), U1.F3 (MGTAVTT), U1.G2 (MGTAVTT), U6.9 (OUT), U6.10 (OUT)
unnamed: R16.2, U1.A6 (MGTRREF_216)
unnamed: C3.2, R1.2, R2.1, U2.5 (FB)
unnamed: C14.2, R4.2, R5.1, U3.5 (FB)
unnamed: C23.2, R7.2, R8.1, U4.5 (FB)
unnamed: R10.2, R11.1, U5.8 (FB)
unnamed: C46.1, U5.7 (SS)
unnamed: R13.2, R14.1, U6.8 (FB)
unnamed: C50.1, U6.7 (SS)
unnamed: C84.1, U12.5 (CT)
PG_AUX_1V8: R6.2, U3.11 (PG), U4.3 (EN), U13.3 (EN)
PG_CORE_1V0: R3.2, U2.11 (PG), U3.3 (EN)
PG_GTP_1V4: R43.2, U5.5 (EN), U13.11 (PG)
PG_MGT_1V0: R12.2, U5.3 (PG), U6.5 (EN)
PWR_DVDT: C77.1, U10.7 (dVdt)
PWR_EN_UVLO: R34.2, R35.1, U10.1 (EN/UVLO)
PWR_ILM: R37.1, U10.9 (ILM)
PWR_OVLO: R35.2, R36.1, U10.2 (OVLO)
SPI_LATCH_SHARED: J1.59, U1.U1 (L15N_T2_DQS)
STIM_CHB_SHARED: J2.59, U1.F14 (L22N_T3_A16)
STIM_CLK_SHARED: J2.56, U1.G14 (L22P_T3_A17)
STIM_EN_SHARED: J2.58, U1.U6 (L20P_T3)
STIM_START_SHARED: J2.57, U1.V9 (L24N_T3_A00_D16)
VCCADC_1V8: C57.1, L1.2, U1.J10 (VCCADC_0)
VCCAUX_1V8: C13.1, C14.1, C15.1, C16.1, C17.1, C18.1, C19.1, C20.1, C58.1, C59.1, C60.1, C62.1, C80.1, C81.1, L1.1, R4.1, R17.1, R18.1, R20.1, R21.1, R22.1, R27.1, R38.1, R45.1, R49.1, R53.1, TP5.1 (PAD_1), TP9.1 (PAD_1), U1.E10 (VCCO_0), U1.G12 (VCCAUX_[5_balls]), U1.H13 (VCCAUX), U1.K13 (VCCAUX), U1.M13 (VCCAUX), U1.P13 (VCCAUX), U1.R10 (VCCO_0), U1.R12 (M0_0), U3.6 (OUT_S), U3.9 (OUT), U3.10 (OUT), U7.8 (VCC_1.8_V), U8.13 (VCCB_1V8), Y1.1 (OE), Y1.6 (VDD)
VCCINT_1V0: C2.1, C3.1, C4.1, C5.1, C6.1, C7.1, C8.1, C9.1, C10.1, C11.1, R1.1, TP4.1 (PAD_1), U1.F7 (VCCINT_1V0), U1.F9 (VCCINT_1V0), U1.F11 (VCCBRAM/VCCINT_[21_balls]), U1.G8 (VCCINT_1V0), U1.G10 (VCCBRAM_1V0), U1.H7 (VCCINT_1V0), U1.H9 (VCCINT_1V0), U1.H11 (VCCBRAM_1V0), U1.J8 (VCCINT_1V0), U1.J12 (VCCINT_1V0), U1.K7 (VCCINT_1V0), U1.K11 (VCCINT_1V0), U1.L8 (VCCINT_1V0), U1.L12 (VCCINT_1V0), U1.M7 (VCCINT_1V0), U1.M11 (VCCINT_1V0), U1.N8 (VCCINT_1V0), U1.N10 (VCCINT_1V0), U1.N12 (VCCINT_1V0), U1.P9 (VCCINT_1V0), U1.P11 (VCCINT_1V0), U2.6 (OUT_S), U2.9 (OUT), U2.10 (OUT)
VCCO_1V5: C22.1, C23.1, C24.1, C25.1, C26.1, C27.1, C28.1, C29.1, C30.1, C31.1, C32.1, C33.1, C34.1, C35.1, C36.1, C37.1, C38.1, C39.1, C40.1, C41.1, C42.1, C61.1, C63.1, L3.1, R7.1, R19.1, R25.1, R48.1, R50.1, TP6.1 (PAD_1), U1.A16 (VCCO), U1.B13 (VCCO), U1.C10 (VCCO), U1.D17 (VCCO), U1.E14 (VCCO), U1.G18 (VCCO), U1.H15 (VCCO), U1.L6 (VCCO), U1.L16 (VCCO), U1.M3 (VCCO), U1.P7 (VCCO), U1.P17 (VCCO), U1.R4 (VCCO), U1.R14 (VCCO), U1.T1 (VCCO), U1.T11 (VCCO), U1.U8 (VCCO), U1.U18 (VCCO), U1.V5 (VCCO), U1.V15 (VCCO), U4.6 (OUT_S), U4.9 (OUT), U4.10 (OUT), U8.5 (DIR3_H), U8.14 (VCCA_1V5), U8.15 (DIR1_H), U8.16 (DIR2_H), U14.5 (VCC_1V5)
VIN_3V3: C1.1, C12.1, C21.1, C44.1, C48.1, C76.1, C82.1, C83.1, C85.1, J1.60, R3.1, R6.1, R9.1, R12.1, R39.1, R43.1, R47.1, TP3.1 (PAD_1), U2.3 (EN), U2.12 (IN), U2.13 (IN), U2.14 (IN), U3.12 (IN), U3.13 (IN), U3.14 (IN), U4.12 (IN), U4.13 (IN), U4.14 (IN), U5.4 (BIAS), U6.4 (BIAS), U10.6 (OUT), U11.5 (VCC_3V3), U12.4 (VDD_3V3), U13.12 (IN), U13.13 (IN), U13.14 (IN)
